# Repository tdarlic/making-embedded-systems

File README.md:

# Making Embedded Systems class
 ORANGE STARS - Mar/Apr/May/June 2022

 Following are links to weekly assignments:
- [Week 1](/Week1/README.md)
- [Week 2](/Week2/README.md)
- [Week 3](/Week3/README.md)
- [Week 4](/Week4/README.md)
- [Week 5](/Week5/README.md)
- [Week 6](/Week6/README.md)
- [Week 7](/Week7/README.md)
- [Week 8](/Week8/README.md)
- [Week 9](/Week9/README.md)

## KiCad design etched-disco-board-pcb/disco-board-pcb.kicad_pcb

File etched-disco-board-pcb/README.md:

# DISCO board prototype PCB

This board plugs into the DISCO-F429ZI prototype board

Following devices are added:
1. LPS28DFW Barometer 
    - [Info Page](https://www.st.com/en/mems-and-sensors/lps28dfw.html#documentation)
    - [Firmware Drivers](https://github.com/STMicroelectronics/STMems_Standard_C_drivers)
2. MMA8653FC Accelerometer
    - [Info Page](https://www.nxp.com/products/sensors/accelerometers/2g-4g-8g-low-g-10-bit-digital-accelerometer:MMA8653FC)

### Schematic

### PCB Top View

### PCB Bottom View

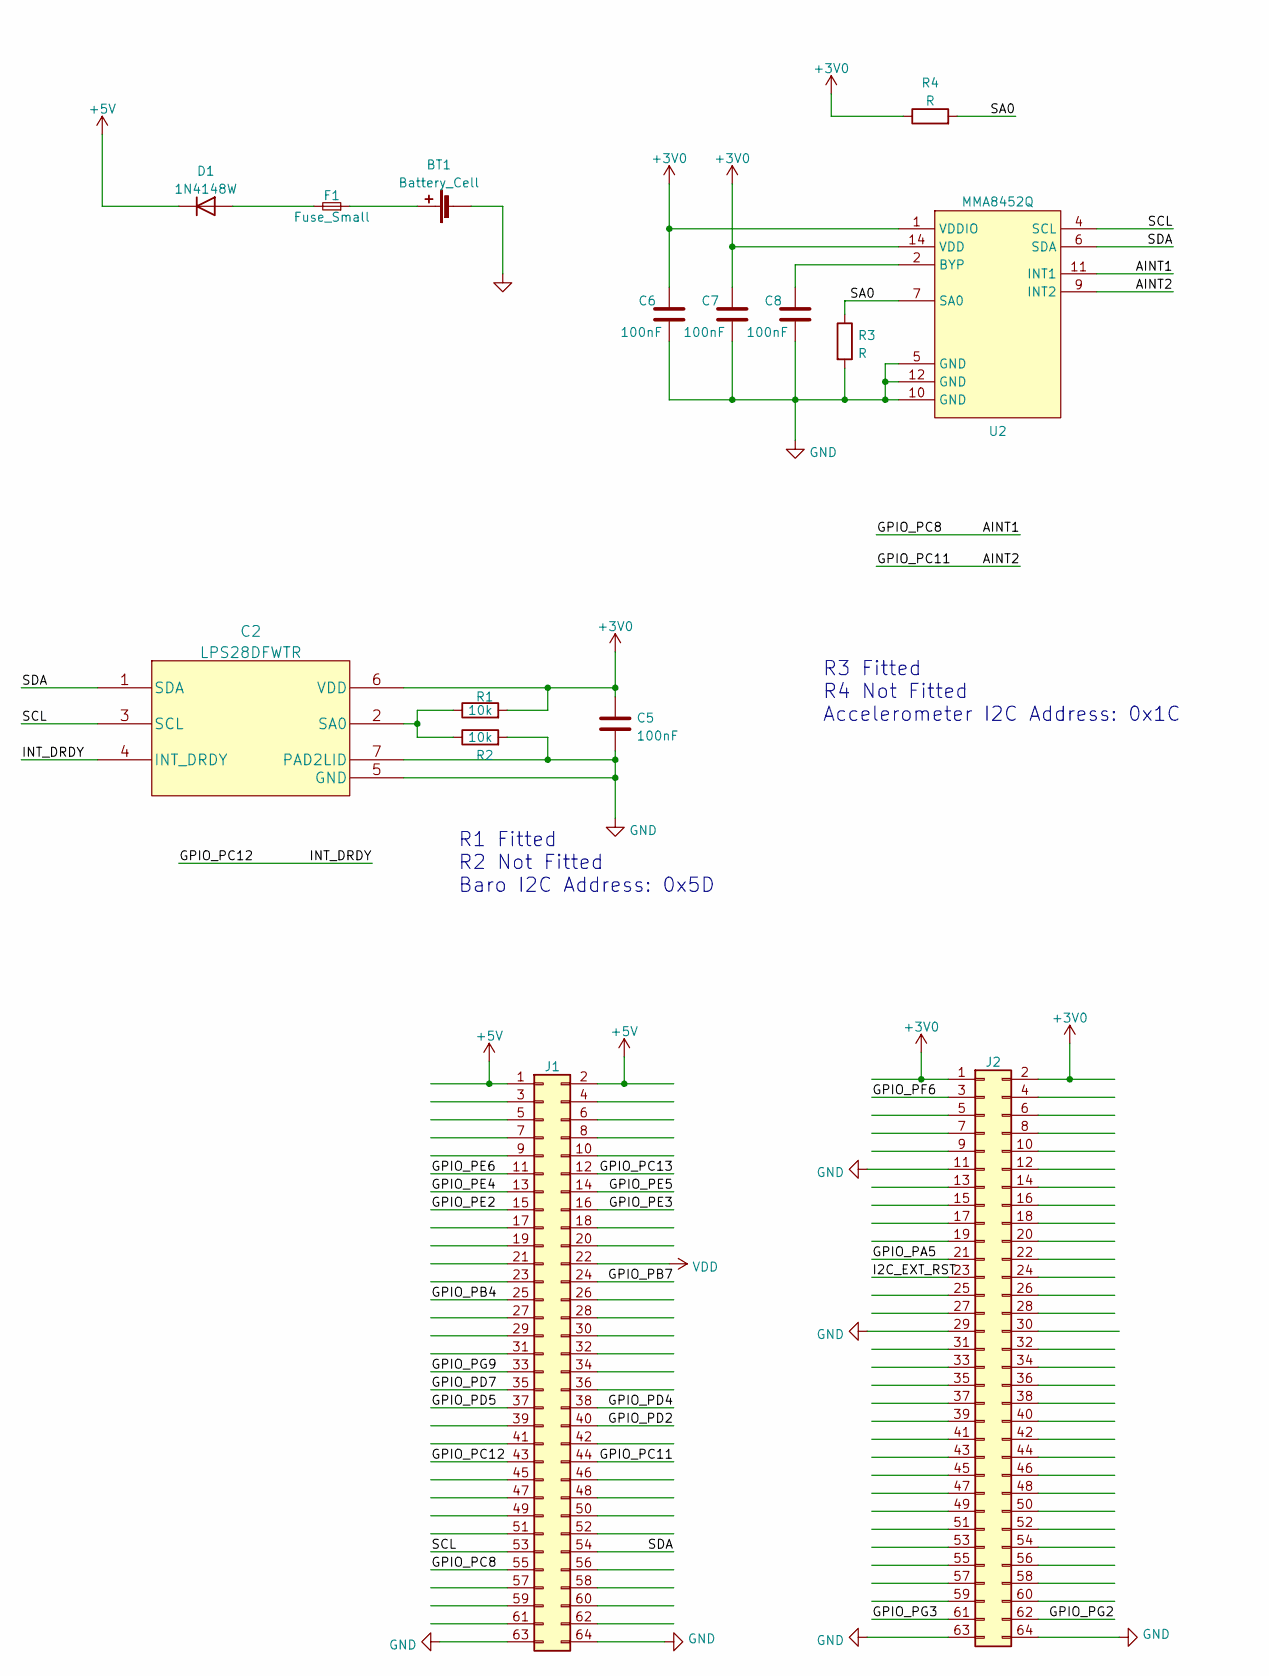
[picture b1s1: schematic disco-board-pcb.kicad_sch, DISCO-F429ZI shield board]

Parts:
BT1: Battery_Cell; BatteryHolder_MPD_BH-18650-PC2
C2: LPS28DFWTR
C5, C6, C7, C8: 100nF; C_0603_1608Metric_Pad1.05x0.95mm
D1: 1N4148W; D_SOD-123
F1: Fuse_Small; Fuse_1206_3216Metric
J1, J2: Conn_02x32_Odd_Even; PinSocket_2x32_P2.54mm_Vertical
R1, R2: 10k; R_0805_2012Metric_Pad1.20x1.40mm
R3, R4: R; R_0805_2012Metric_Pad1.20x1.40mm
U2: MMA8452Q; LGA16_BRAKEOUT

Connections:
+3V0: C2.6 (VDD), C5.1, C6.1, C7.1, J2.1, J2.2, R1.2, R4.1, U2.1 (VDDIO), U2.14 (VDD)
+5V: D1.1 (K), J1.1, J1.2
/AINT1: J1.55, U2.11 (INT1)
/AINT2: J1.44, U2.9 (INT2)
/GPIO_PA5: J2.21
/GPIO_PB4: J1.25
/GPIO_PB7: J1.24
/GPIO_PC12: C2.4 (INT_DRDY), J1.43
/GPIO_PC13: J1.12
/GPIO_PD2: J1.40
/GPIO_PD4: J1.38
/GPIO_PD5: J1.37
/GPIO_PD7: J1.35
/GPIO_PE2: J1.15
/GPIO_PE3: J1.16
/GPIO_PE4: J1.13
/GPIO_PE5: J1.14
/GPIO_PE6: J1.11
/GPIO_PF6: J2.3
/GPIO_PG2: J2.62
/GPIO_PG3: J2.61
/GPIO_PG9: J1.33
/I2C_EXT_RST: J2.23
/SA0: R3.1, R4.2, U2.7 (SA0)
/SCL: C2.3 (SCL), J1.53, U2.4 (SCL)
/SDA: C2.1 (SDA), J1.54, U2.6 (SDA)
GND: BT1.2 (-), C2.5 (GND), C2.7 (PAD2LID), C5.2, C6.2, C7.2, C8.2, J1.63, J1.64, J2.11, J2.29, J2.63, J2.64, R2.2, R3.2, U2.5 (GND), U2.10 (GND), U2.12 (GND)
unnamed: BT1.1 (+), F1.1
unnamed: C2.2 (SA0), R1.1, R2.1
unnamed: C8.1, U2.2 (BYP)
unnamed: D1.2 (A), F1.2
VDD: J1.22

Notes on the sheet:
R1 Fitted R2 Not Fitted Baro I2C Address: 0x5D
R3 Fitted R4 Not Fitted Accelerometer I2C Address: 0x1C

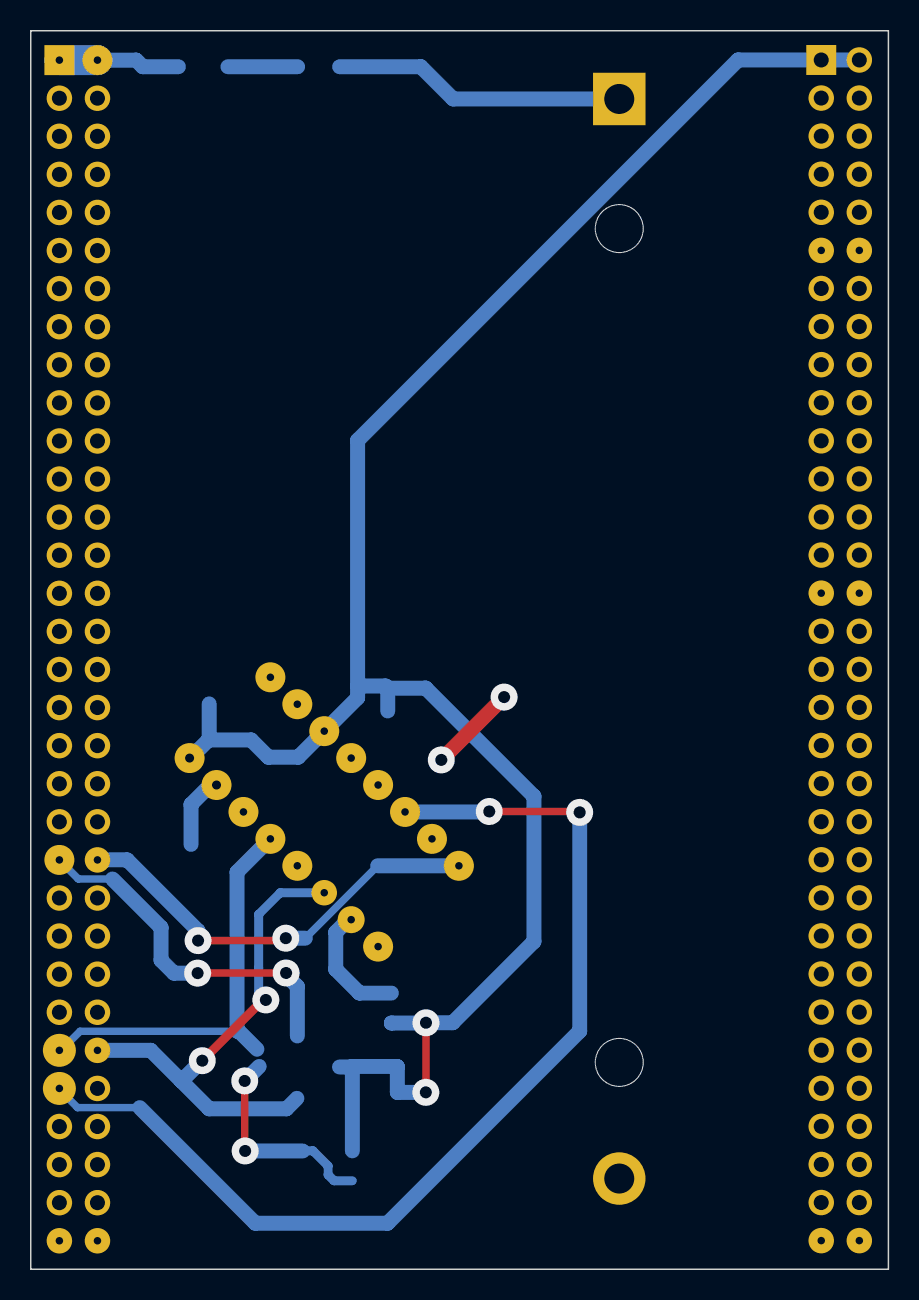
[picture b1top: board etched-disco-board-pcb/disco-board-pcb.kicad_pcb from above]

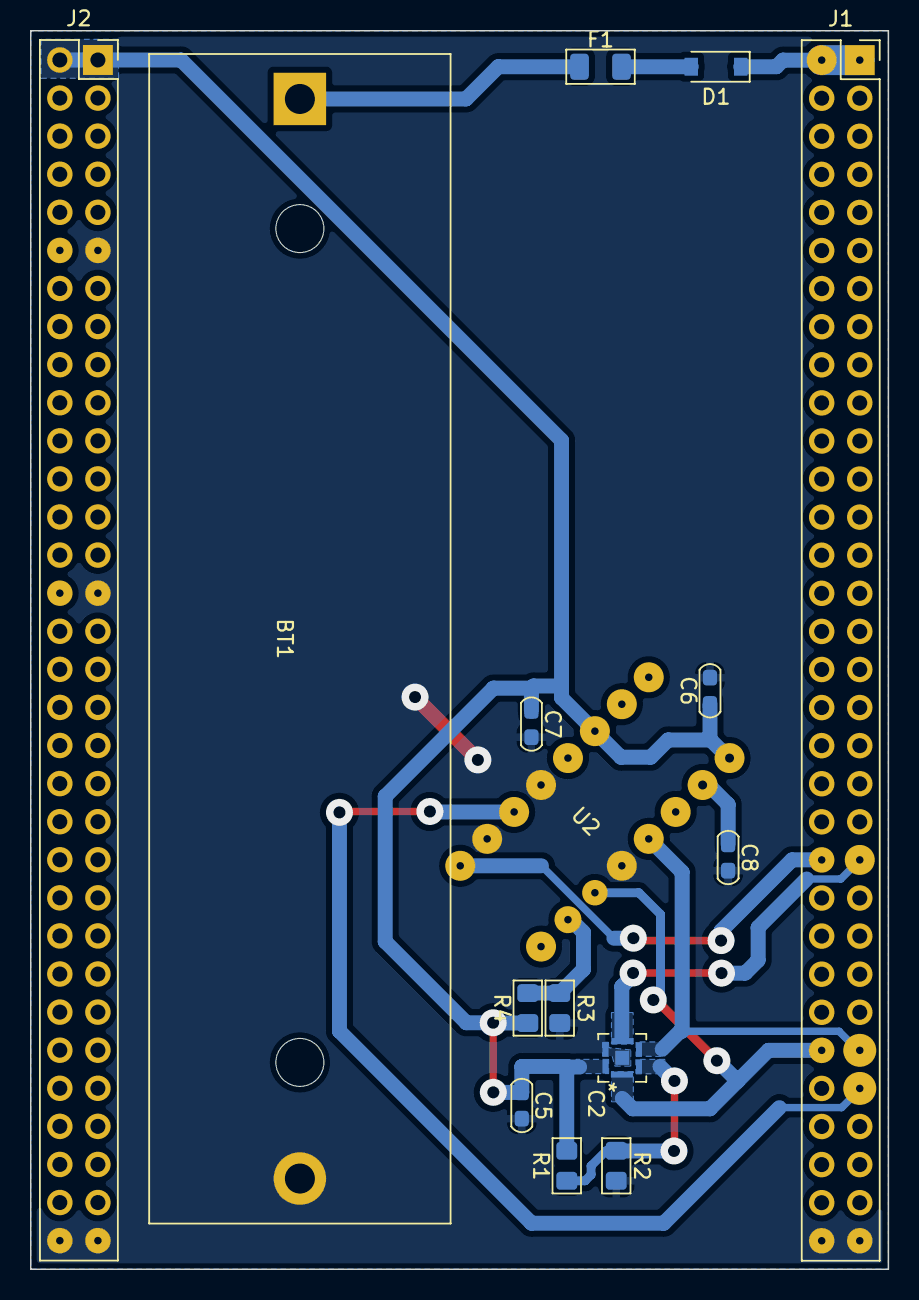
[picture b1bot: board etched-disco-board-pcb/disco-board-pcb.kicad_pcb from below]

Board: 2 copper layers, 57.2 x 82.6 mm, 15 parts (15 on the bottom side), 13 nets.

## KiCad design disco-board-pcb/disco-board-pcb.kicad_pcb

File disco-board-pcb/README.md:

# DISCO board prototype PCB

This board plugs into the DISCO-F429ZI prototype board

Following devices are added:
1. LPS28DFW Barometer 
    - [Info Page](https://www.st.com/en/mems-and-sensors/lps28dfw.html#documentation)
    - [Firmware Drivers](https://github.com/STMicroelectronics/STMems_Standard_C_drivers)
2. MMA8653FC Accelerometer
    - [Info Page](https://www.nxp.com/products/sensors/accelerometers/2g-4g-8g-low-g-10-bit-digital-accelerometer:MMA8653FC)

### Schematic

### PCB Top View

### PCB Bottom View

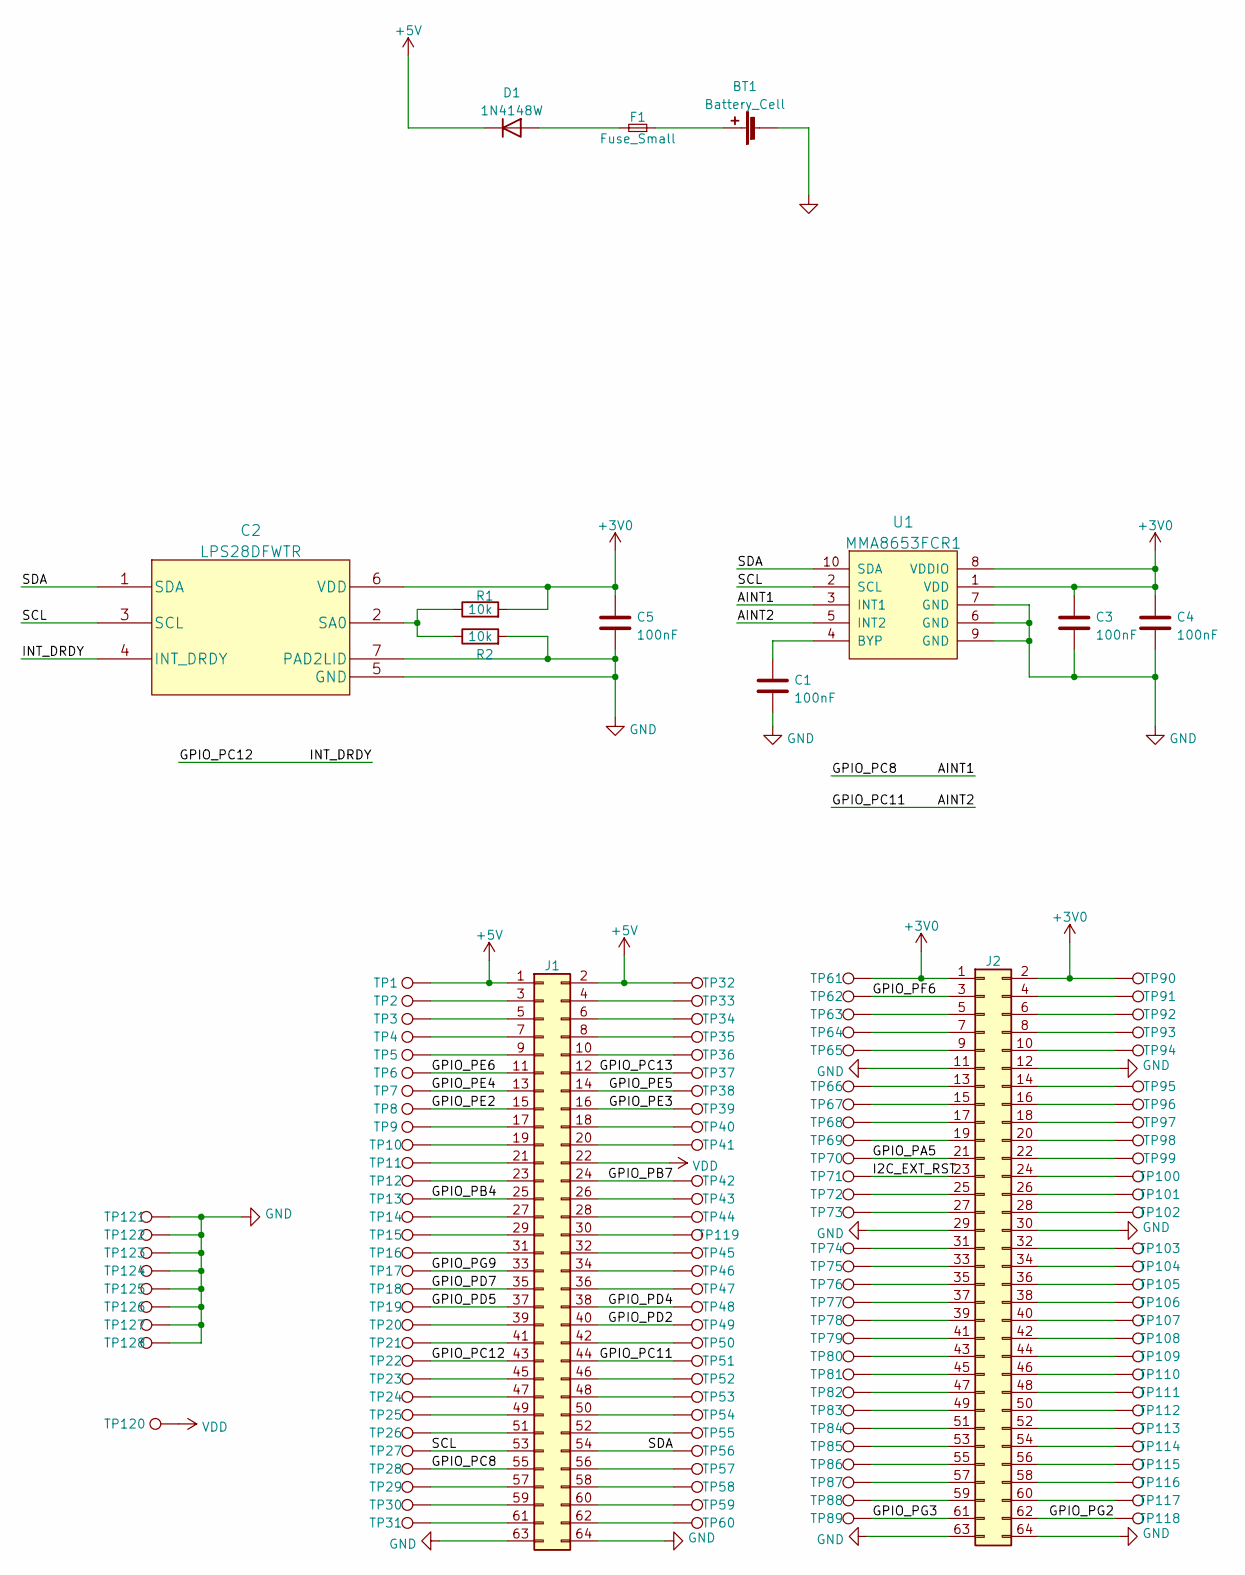
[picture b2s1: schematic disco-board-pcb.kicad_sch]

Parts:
BT1: Battery_Cell; BatteryHolder_MPD_BH-18650-PC2
C1, C3, C4, C5: 100nF; C_0603_1608Metric_Pad1.05x0.95mm
C2: LPS28DFWTR
D1: 1N4148W; D_SOD-123
F1: Fuse_Small; Fuse_1206_3216Metric
J1, J2: Conn_02x32_Odd_Even; PinSocket_2x32_P2.54mm_Vertical
R1, R2: 10k; R_0603_1608Metric_Pad1.05x0.95mm
TP1, TP2, TP3, TP4, TP5, TP6, TP7, TP8, TP9, TP10, TP11, TP12, TP13, TP14, TP15, TP16, TP17, TP18, TP19, TP20, TP21, TP22, TP23, TP24, TP25, TP26, TP27, TP28, TP29, TP30, TP31, TP32, TP33, TP34, TP35, TP36, TP37, TP38, TP39, TP40, TP41, TP42, TP43, TP44, TP45, TP46, TP47, TP48, TP49, TP50, TP51, TP52, TP53, TP54, TP55, TP56, TP57, TP58, TP59, TP60, TP61, TP62, TP63, TP64, TP65, TP66, TP67, TP68, TP69, TP70, TP71, TP72, TP73, TP74, TP75, TP76, TP77, TP78, TP79, TP80, TP81, TP82, TP83, TP84, TP85, TP86, TP87, TP88, TP89, TP90, TP91, TP92, TP93, TP94, TP95, TP96, TP97, TP98, TP99, TP100, TP101, TP102, TP103, TP104, TP105, TP106, TP107, TP108, TP109, TP110, TP111, TP112, TP113, TP114, TP115, TP116, TP117, TP118, TP119, TP120, TP121, TP122, TP123, TP124, TP125, TP126, TP127, TP128: TestPoint; TestPoint_Pad_D1.5mm
U1: MMA8653FCR1; DFN-10_2x2mm_P0.4mm

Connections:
+3V0: C2.6 (VDD), C3.1, C4.1, C5.1, J2.1, J2.2, R1.2, TP61.1, TP90.1, U1.1 (VDD), U1.8 (VDDIO)
+5V: D1.1 (K), J1.1, J1.2, TP1.1, TP32.1
/AINT1: J1.55, TP28.1, U1.3 (INT1)
/AINT2: J1.44, TP51.1, U1.5 (INT2)
/GPIO_PA5: J2.21, TP70.1
/GPIO_PB4: J1.25, TP13.1
/GPIO_PB7: J1.24, TP42.1
/GPIO_PC12: C2.4 (INT_DRDY), J1.43, TP22.1
/GPIO_PC13: J1.12, TP37.1
/GPIO_PD2: J1.40, TP49.1
/GPIO_PD4: J1.38, TP48.1
/GPIO_PD5: J1.37, TP19.1
/GPIO_PD7: J1.35, TP18.1
/GPIO_PE2: J1.15, TP8.1
/GPIO_PE3: J1.16, TP39.1
/GPIO_PE4: J1.13, TP7.1
/GPIO_PE5: J1.14, TP38.1
/GPIO_PE6: J1.11, TP6.1
/GPIO_PF6: J2.3, TP62.1
/GPIO_PG2: J2.62, TP118.1
/GPIO_PG3: J2.61, TP89.1
/GPIO_PG9: J1.33, TP17.1
/I2C_EXT_RST: J2.23, TP71.1
/SCL: C2.3 (SCL), J1.53, TP27.1, U1.2 (SCL)
/SDA: C2.1 (SDA), J1.54, TP56.1, U1.10 (SDA)
GND: BT1.2 (-), C1.2, C2.5 (GND), C2.7 (PAD2LID), C3.2, C4.2, C5.2, J1.63, J1.64, J2.11, J2.12, J2.29, J2.30, J2.63, J2.64, R2.2, TP121.1, TP122.1, TP123.1, TP124.1, TP125.1, TP126.1, TP127.1, TP128.1, U1.6 (GND), U1.7 (GND), U1.9 (GND)
unnamed: BT1.1 (+), F1.1
unnamed: C1.1, U1.4 (BYP)
unnamed: C2.2 (SA0), R1.1, R2.1
unnamed: D1.2 (A), F1.2
unnamed: J1.3, TP2.1
unnamed: J1.4, TP33.1
unnamed: J1.5, TP3.1
unnamed: J1.6, TP34.1
unnamed: J1.7, TP4.1
unnamed: J1.8, TP35.1
unnamed: J1.9, TP5.1
unnamed: J1.10, TP36.1
unnamed: J1.17, TP9.1
unnamed: J1.18, TP40.1
unnamed: J1.19, TP10.1
unnamed: J1.20, TP41.1
unnamed: J1.21, TP11.1
unnamed: J1.23, TP12.1
unnamed: J1.26, TP43.1
unnamed: J1.27, TP14.1
unnamed: J1.28, TP44.1
unnamed: J1.29, TP15.1
unnamed: J1.30, TP119.1
unnamed: J1.31, TP16.1
unnamed: J1.32, TP45.1
unnamed: J1.34, TP46.1
unnamed: J1.36, TP47.1
unnamed: J1.39, TP20.1
unnamed: J1.41, TP21.1
unnamed: J1.42, TP50.1
unnamed: J1.45, TP23.1
unnamed: J1.46, TP52.1
unnamed: J1.47, TP24.1
unnamed: J1.48, TP53.1
unnamed: J1.49, TP25.1
unnamed: J1.50, TP54.1
unnamed: J1.51, TP26.1
unnamed: J1.52, TP55.1
unnamed: J1.56, TP57.1
unnamed: J1.57, TP29.1
unnamed: J1.58, TP58.1
unnamed: J1.59, TP30.1
unnamed: J1.60, TP59.1
unnamed: J1.61, TP31.1
unnamed: J1.62, TP60.1
unnamed: J2.4, TP91.1
unnamed: J2.5, TP63.1
unnamed: J2.6, TP92.1
unnamed: J2.7, TP64.1
unnamed: J2.8, TP93.1
unnamed: J2.9, TP65.1
unnamed: J2.10, TP94.1
unnamed: J2.13, TP66.1
unnamed: J2.14, TP95.1
unnamed: J2.15, TP67.1
unnamed: J2.16, TP96.1
unnamed: J2.17, TP68.1
unnamed: J2.18, TP97.1
unnamed: J2.19, TP69.1
unnamed: J2.20, TP98.1
unnamed: J2.22, TP99.1
unnamed: J2.24, TP100.1
unnamed: J2.25, TP72.1
unnamed: J2.26, TP101.1
unnamed: J2.27, TP73.1
unnamed: J2.28, TP102.1
unnamed: J2.31, TP74.1
unnamed: J2.32, TP103.1
unnamed: J2.33, TP75.1
unnamed: J2.34, TP104.1
unnamed: J2.35, TP76.1
unnamed: J2.36, TP105.1
unnamed: J2.37, TP77.1
unnamed: J2.38, TP106.1
unnamed: J2.39, TP78.1
unnamed: J2.40, TP107.1
unnamed: J2.41, TP79.1
unnamed: J2.42, TP108.1
unnamed: J2.43, TP80.1
unnamed: J2.44, TP109.1
unnamed: J2.45, TP81.1
unnamed: J2.46, TP110.1
unnamed: J2.47, TP82.1
unnamed: J2.48, TP111.1
unnamed: J2.49, TP83.1
unnamed: J2.50, TP112.1
unnamed: J2.51, TP84.1
unnamed: J2.52, TP113.1
unnamed: J2.53, TP85.1
unnamed: J2.54, TP114.1
unnamed: J2.55, TP86.1
unnamed: J2.56, TP115.1
unnamed: J2.57, TP87.1
unnamed: J2.58, TP116.1
unnamed: J2.59, TP88.1
unnamed: J2.60, TP117.1
VDD: J1.22, TP120.1

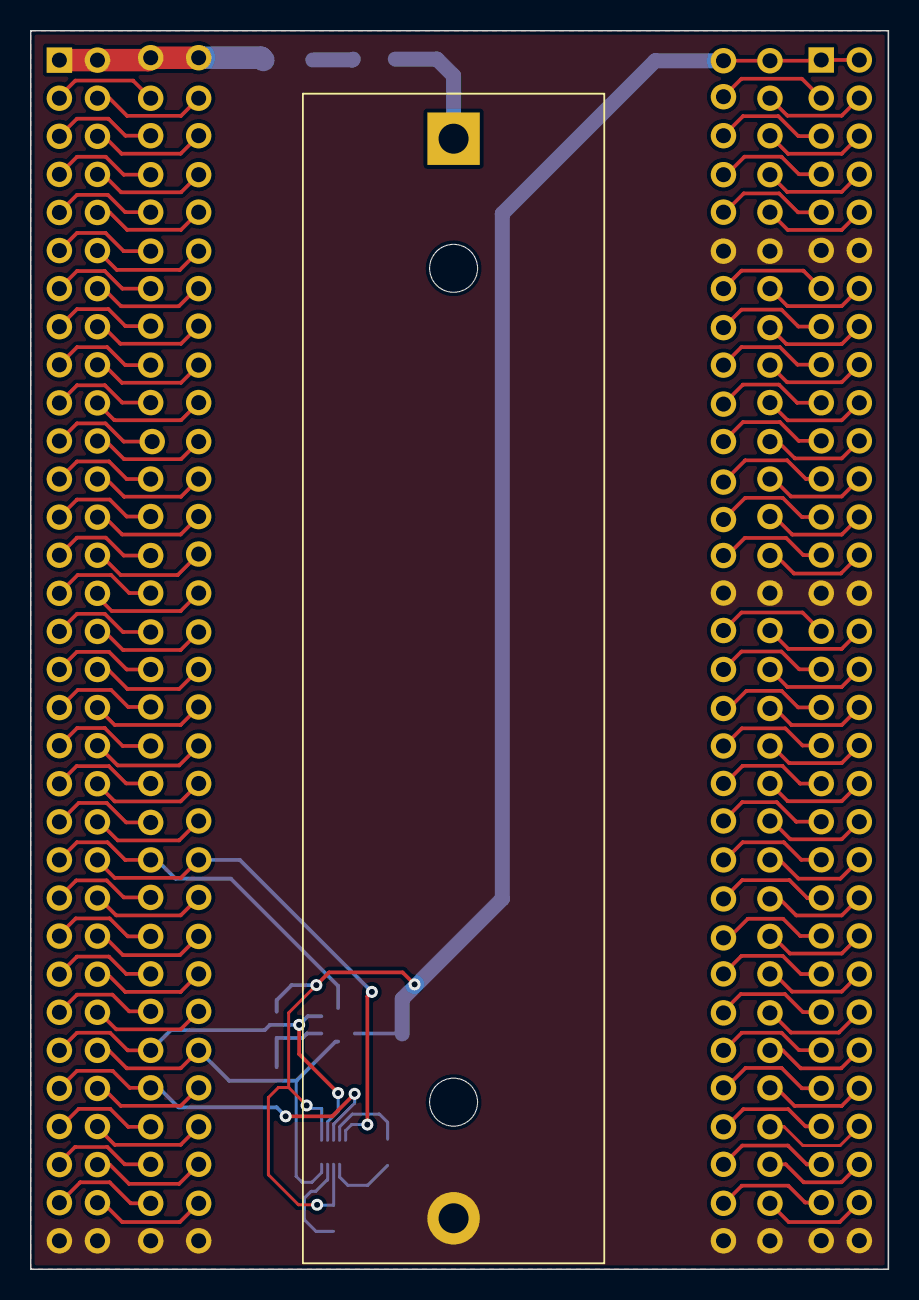
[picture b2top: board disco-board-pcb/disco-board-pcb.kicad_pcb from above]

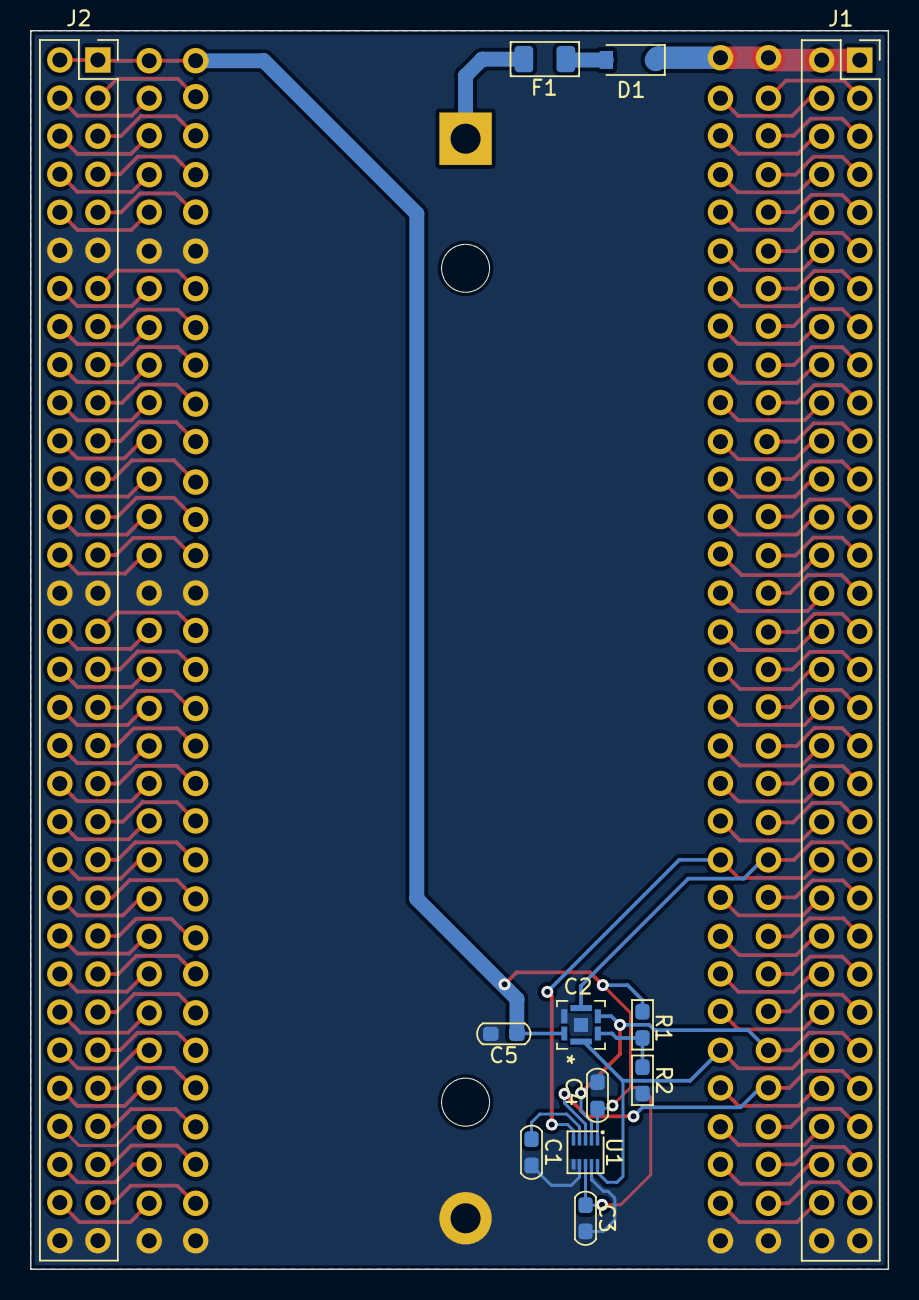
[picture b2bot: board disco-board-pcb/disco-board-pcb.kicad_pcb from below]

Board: 2 copper layers, 57.2 x 82.6 mm, 141 parts (12 on the bottom side), 123 nets.

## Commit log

2022-03-26 Adding first week homework file
2022-03-26 Adding images
2022-03-26 Formatting image names
2022-03-26 Adding Hierarchy_of_control_diagram.drawio
2022-03-26 Formatting images
2022-03-26 Adding layered software diagram
2022-03-31 Adding homework for week 2
2022-03-31 Adding chapter numbers
2022-04-08 Adding Week 3 homework
2022-04-08 Modify add code
2022-04-08 Describing the debunce
2022-04-08 Describing the registers and stepping trough code
2022-04-08 Describing the registers
2022-04-08 Adding debug screenshot
2022-04-08 Chaned line ot GPIO
2022-04-08 Adding submodule BlinkySchmlinky to Week3 containing the code
2022-04-08 Adding link to submodule
2022-04-08 Correcting link to submodule
2022-04-08 Adding small fixes
2022-04-30 Adding week 4 readme
2022-04-30 Adding week 5
2022-04-30 Adding mes-console submodule
2022-04-30 Adding readme
2022-05-01 Updating mes-console
2022-05-13 Adding gitignore
2022-05-13 Adding PCB and week 6 homework
2022-05-14 Completing homework for week 7
2022-05-14 Adding PCB description and documentation
2022-05-14 Correcting readme
2022-05-14 Completing schematic and putting test points on PCB
2022-05-14 Started routing
2022-05-15 Routed all test points
2022-05-15 Completed routing the board
2022-05-15 Adding gerbers and completing saving schematic
2022-05-15 Creating zipped gerber Ordered 15-05-2022
2022-05-15 Adding week 4 state machine table
2022-05-15 Describing the states
2022-05-15 Describing events
2022-05-15 Correcting the name of the week in week 6 homework
2022-05-15 Adding google docs link for the state machine table
2022-05-15 Adding schematic and images to pcb files
2022-05-15 Fixing readme for PCB
2022-05-16 Adding png image of the PCB Small changes
2022-05-16 Adding headers for week 6
2022-05-16 Adding hardware_block_diagram.png
2022-05-16 Week 6 adding description and describing hardware
2022-05-16 Formatting
2022-05-16 Hardware block diagram in color
2022-05-16 Resetting hardware_block_diagram
2022-05-16 Adding main TOC
2022-05-17 Adding software desctription to week 6
2022-05-17 Adding links for libraries
2022-05-17 Adding decription of the libraries and the Hierarchy of control diagram
2022-05-17 Correcting licence line
2022-05-17 Adding dark and light mode for hierarchy_of_control_diagram
2022-05-17 Correcting typos and adding hardware_block_diagram for dark mode
2022-05-22 Adding week 8
2022-05-22 Week 8 commit start writing
2022-05-22 Completing the homework
2022-05-22 Correcting small errors
2022-05-22 Adding submodule with the code
2022-05-22 Adding reference to submodule
2022-05-28 Adding .gitignore
2022-05-28 Adding Week 9 submission code Adding code.c with excercise code Adding gentable.c with code that generates the table
2022-05-28 Adding profiler and started adding explanations to the excercise
2022-05-28 Fixing formatting
2022-05-28 Adding function F and profiling it
2022-05-28 Completing and documenting all functions
2022-05-28 Adding assembly and code length
2022-05-28 Adding length from map file and small fixes
2022-05-28 Fixing table
2022-05-28 Adding function descriptions in a table
2022-05-28 Formatting table
2022-05-28 Formatting table headers
2022-05-28 Adding speed into table
2022-05-28 Formatting header
2022-05-28 Correcting small tipfelers
2022-05-28 Fixing table headers
2022-05-28 Adding links to weeks in main readme
2022-05-28 Fixing links
2022-05-30 Adding hand etched board for testing
2022-05-30 Correcting error in PCB where NRST was connected to GND on etched-disco-board-pcb
2022-05-31 Small changes in PCB

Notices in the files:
parts and their libraries:
Copyright 2021 Accelerated Designs. All rights reserved.
